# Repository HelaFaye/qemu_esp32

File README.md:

# qemu_esp32: ESP32 boards in QEMU, for firmware developers

Run your ESP32-S3 firmware, unmodified, on an emulated board: the chip's peripherals, the
parts you wire to it (displays, touch, SD cards, LoRa radios, buttons, I/O expanders,
keyboards, OLEDs) and the radio links between boards (LoRa, Bluetooth). Test drivers, UIs
and protocols before there's hardware; script what a person would do (press a button,
touch the screen, type, carry a node out of range) and check what the firmware does (its
serial output, its screen, what it sends over the air); and run it all in CI.

Then stress it the way the real world will: weak and crowded radio, noise on the wires,
brown-outs and power cuts, parts losing power, glitched instructions, with the board read
straight from your KiCad design. The aim is to find a design's weaknesses before ordering
a PCB, buying parts or wiring a breadboard.

Every model is built from the chip's register definitions and the drivers that use them
(ESP-IDF, Arduino), and tested the way those drivers drive it. Real projects' firmware
runs on it as test cases.

## Quick start

```sh
patches/espressif-qemu/build.sh ~/esp-qemu          # Espressif's QEMU with these patches
export QEMU_XTENSA=~/esp-qemu/build/qemu-system-xtensa
```

```python
import sys; sys.path.insert(0, "firmware")
from boards import boot

node = boot("t-deck", "flash.bin", "/tmp/run")       # A merged image (esptool merge-bin)
node.wait_for(r"Start Radio success", 60)            # Its serial output
node.qmp("qom-set", path="/machine/peripheral/kbd", property="keys", value="hello")
w, h, rgb = node.screendump("/tmp/run/screen.ppm")   # What its display shows
```

Or your own design: `boot("kicad:my-board.kicad_pcb", "flash.bin", "/tmp/run")`.

## Documentation

| | |
|---|---|
| [Getting started](docs/getting-started.md) | Building QEMU, running firmware, its serial ports, screens and inputs, debugging; the Python API |
| [Boards](docs/boards.md) | What's emulated; describing a board (in Python, on the command line, or from KiCad); the boards here |
| [Testing](docs/testing.md) | Real firmware as test cases, the device tests, CI |
| [Stress testing](docs/stress-testing.md) | Radio environments, bus noise, brown-outs, power domains, fault injection: what exists and what's planned |
| [Devices and patches](patches/espressif-qemu/README.md) | Each patch, each device, its properties and lines |

Next to the code: [`firmware/`](firmware/README.md) (the test cases),
[`radio/`](radio/README.md) (the air between LoRa radios),
[`bluetooth/`](bluetooth/README.md) (virtual Bluetooth), [`faults/`](faults/README.md)
(fault injection, power and bus errors), [`kicad/`](kicad/README.md) (boards from KiCad).

## Layout

| Where | What |
|---|---|
| `patches/espressif-qemu/` | The emulation: a patch series for [Espressif's QEMU](https://github.com/espressif/qemu) at the commit in `BASE`; `build.sh` fetches, applies and builds |
| `firmware/boards.py` | Boards as Python, and `boot()`; `firmware/<project>/` the test cases |
| `radio/` | `airhub.py` (LoRa radios in different QEMUs on one air) and `environment.py` (positions, path loss, noise, interferers) |
| `bluetooth/` | Your firmware's own Bluetooth host over HCI to a virtual controller, with virtual phones and controllers as peers |
| `faults/` | Glitches and campaigns (`inject.py`, `campaign.py`), and demos of power and bus errors |
| `kicad/` | `kiboard.py`: a QEMU board from a `.kicad_pcb` or netlist |
| `docs/upstream/`, `examples/` | Ebiroll's original qemu_esp32 (this is a fork of it): [his documentation](docs/upstream/README.md) and examples, kept as they were |

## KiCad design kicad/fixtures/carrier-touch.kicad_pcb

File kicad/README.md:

# Boards from KiCad

`kiboard.py` reads a KiCad design and writes the QEMU board for it: the ESP32-S3, the
parts this emulation has models for, and how they're wired. The design is either the
board file (`.kicad_pcb`: every pad carries its net and, when it came from a schematic,
its pin's name) or a netlist (`kicad-cli sch export netlist`).

```sh
kicad/kiboard.py my-board.kicad_pcb               # what it found, and the QEMU arguments
kicad/kiboard.py my-board.net --python board.py   # a function for firmware/boards.py
```

```python
node = boot("kicad:my-board.kicad_pcb", "flash.bin", "run", sd="card.img")
```

What it does:
- **The chip.** An ESP32-S3 (module or chip) by its value, symbol or footprint; its GPIOs
  by pin name (`IO10`, `GPIO10`, `RXD0`). A WROOM-1 placed without a schematic: by pad,
  from Espressif's pin table. Other ESP32s are reported (the C3 and classic ESP32 have
  QEMU machines but not these board models; the C5, C6, H2, P4 none).
- **Parts.** The displays (ILI9341, ILI9488, ST7789, ST7735, ST7796, GC9A01), touch
  (XPT2046, GT911, CST816, FT6336), SX1262/1261/1268 and modules built on them (E22,
  RA-01S, ...), SD sockets, MCP23017, SSD1306/SH1106, and push buttons to ground. Their
  pins matched by name; a part with no pin names, by its datasheet pinout (MCP23017,
  XPT2046, microSD); a display module on a plain header, by its nets' names (`LCD_CS`,
  `TFT_DC`).
- **Buses.** Parts sharing a clock (SPI) or SDA (I2C) net share a bus, each bus the next
  of the S3's (SPI2, SPI3; I2C0, I2C1). An MCP23017's address from where its A0-A2 go.
- **Lines.** Chip selects, D/C, backlight, BUSY, DIO1, interrupts: linked to the GPIO their
  net reaches, open-drain with a pull-up where the part's line is open-drain.
- **What it can't do, it says.** A chip select or reset that reaches no GPIO, an I2C bus
  without pull-ups, an active-high button, a third SPI bus, parts it doesn't know.

`fixtures/make_carrier.py` builds a test design with KiCad's own `pcbnew` API (gbagate's
touch carrier, with and without pin names); `test_kiboard.py` checks kiboard reads it
back to the hand-written board in `firmware/boards.py`, and that QEMU starts with it.

Next (docs/stress-testing.md, 5): the routing (trace lengths, nets running side by side,
distance to the antenna) into bus-noise rates per net, and a KiCad action plugin.

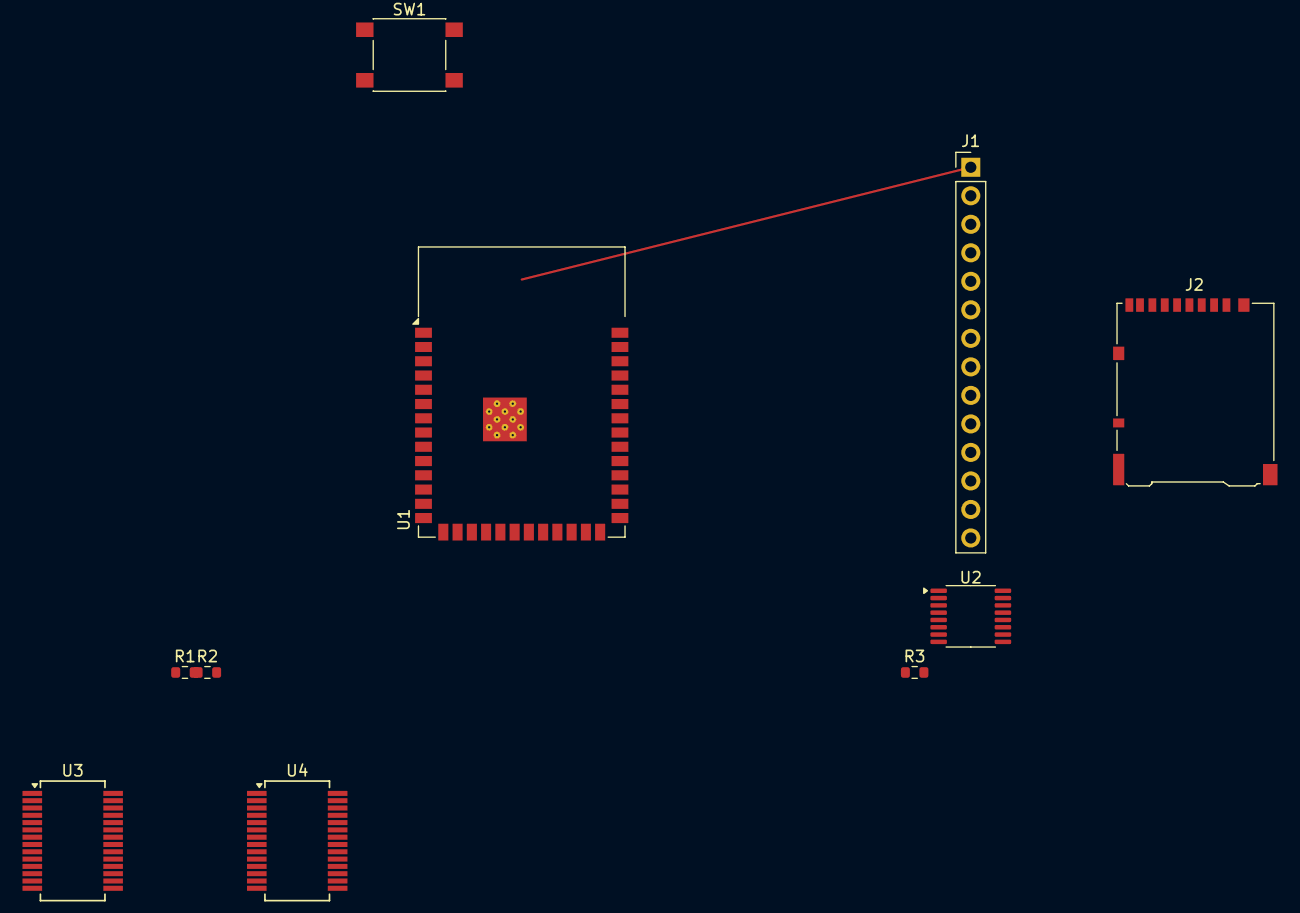
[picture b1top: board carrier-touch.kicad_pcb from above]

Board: 2 copper layers, 10 parts (0 on the bottom side), 15 nets.

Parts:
J1: ILI9341 2.8in module; PinHeader_1x14_P2.54mm_Vertical
J2: Micro_SD_Card; microSD_HC_Hirose_DM3AT-SF-PEJM5
R1, R2: 4.7k; R_0603_1608Metric
R3: 10k; R_0603_1608Metric
SW1: SW_Push; SW_SPST_PTS645
U1: ESP32-S3-WROOM-1
U2: XPT2046; TSSOP-16_4.4x5mm_P0.65mm
U3, U4: MCP23017_SS; SSOP-28_5.3x10.2mm_P0.65mm

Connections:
+3V3: J1.1, J1.8, J2.4 (VDD), R1.2, R2.2, R3.2, U1.2 (3V3), U2.1 (VCC), U2.10 (VCC), U3.9 (VDD), U3.18 (~RESET), U4.9 (VDD), U4.15 (A0), U4.18 (~RESET)
BOOT: SW1.1, U1.27 (IO0)
EXP_INT: U1.29 (IO36), U3.20 (INTA), U4.20 (INTA)
GND: J1.2, J2.6 (VSS), SW1.2, U1.1 (GND), U1.40 (GND), U2.6 (GND), U3.10 (VSS), U3.15 (A0), U3.16 (A1), U3.17 (A2), U4.10 (VSS), U4.16 (A1), U4.17 (A2)
LCD_BL: J1.10, U1.23 (IO21)
LCD_CS: J1.3, U1.18 (IO10)
LCD_DC: J1.5, U1.17 (IO9)
MISO: J1.9, J2.7 (DAT0), U1.21 (IO13), U2.12 (DOUT)
MOSI: J1.6, J2.3 (CMD), U1.19 (IO11), U2.14 (DIN)
SCK: J1.7, J2.5 (CLK), U1.20 (IO12), U2.16 (DCLK)
SCL: R2.1, U1.38 (IO2), U3.12 (SCK), U4.12 (SCK)
SDA: R1.1, U1.39 (IO1), U3.13 (SDA), U4.13 (SDA)
SD_CS: J2.2 (DAT3/CD), U1.8 (IO15)
TOUCH_CS: U1.9 (IO16), U2.15 (~CS)
TOUCH_IRQ: R3.1, U1.10 (IO17), U2.11 (~PENIRQ)
